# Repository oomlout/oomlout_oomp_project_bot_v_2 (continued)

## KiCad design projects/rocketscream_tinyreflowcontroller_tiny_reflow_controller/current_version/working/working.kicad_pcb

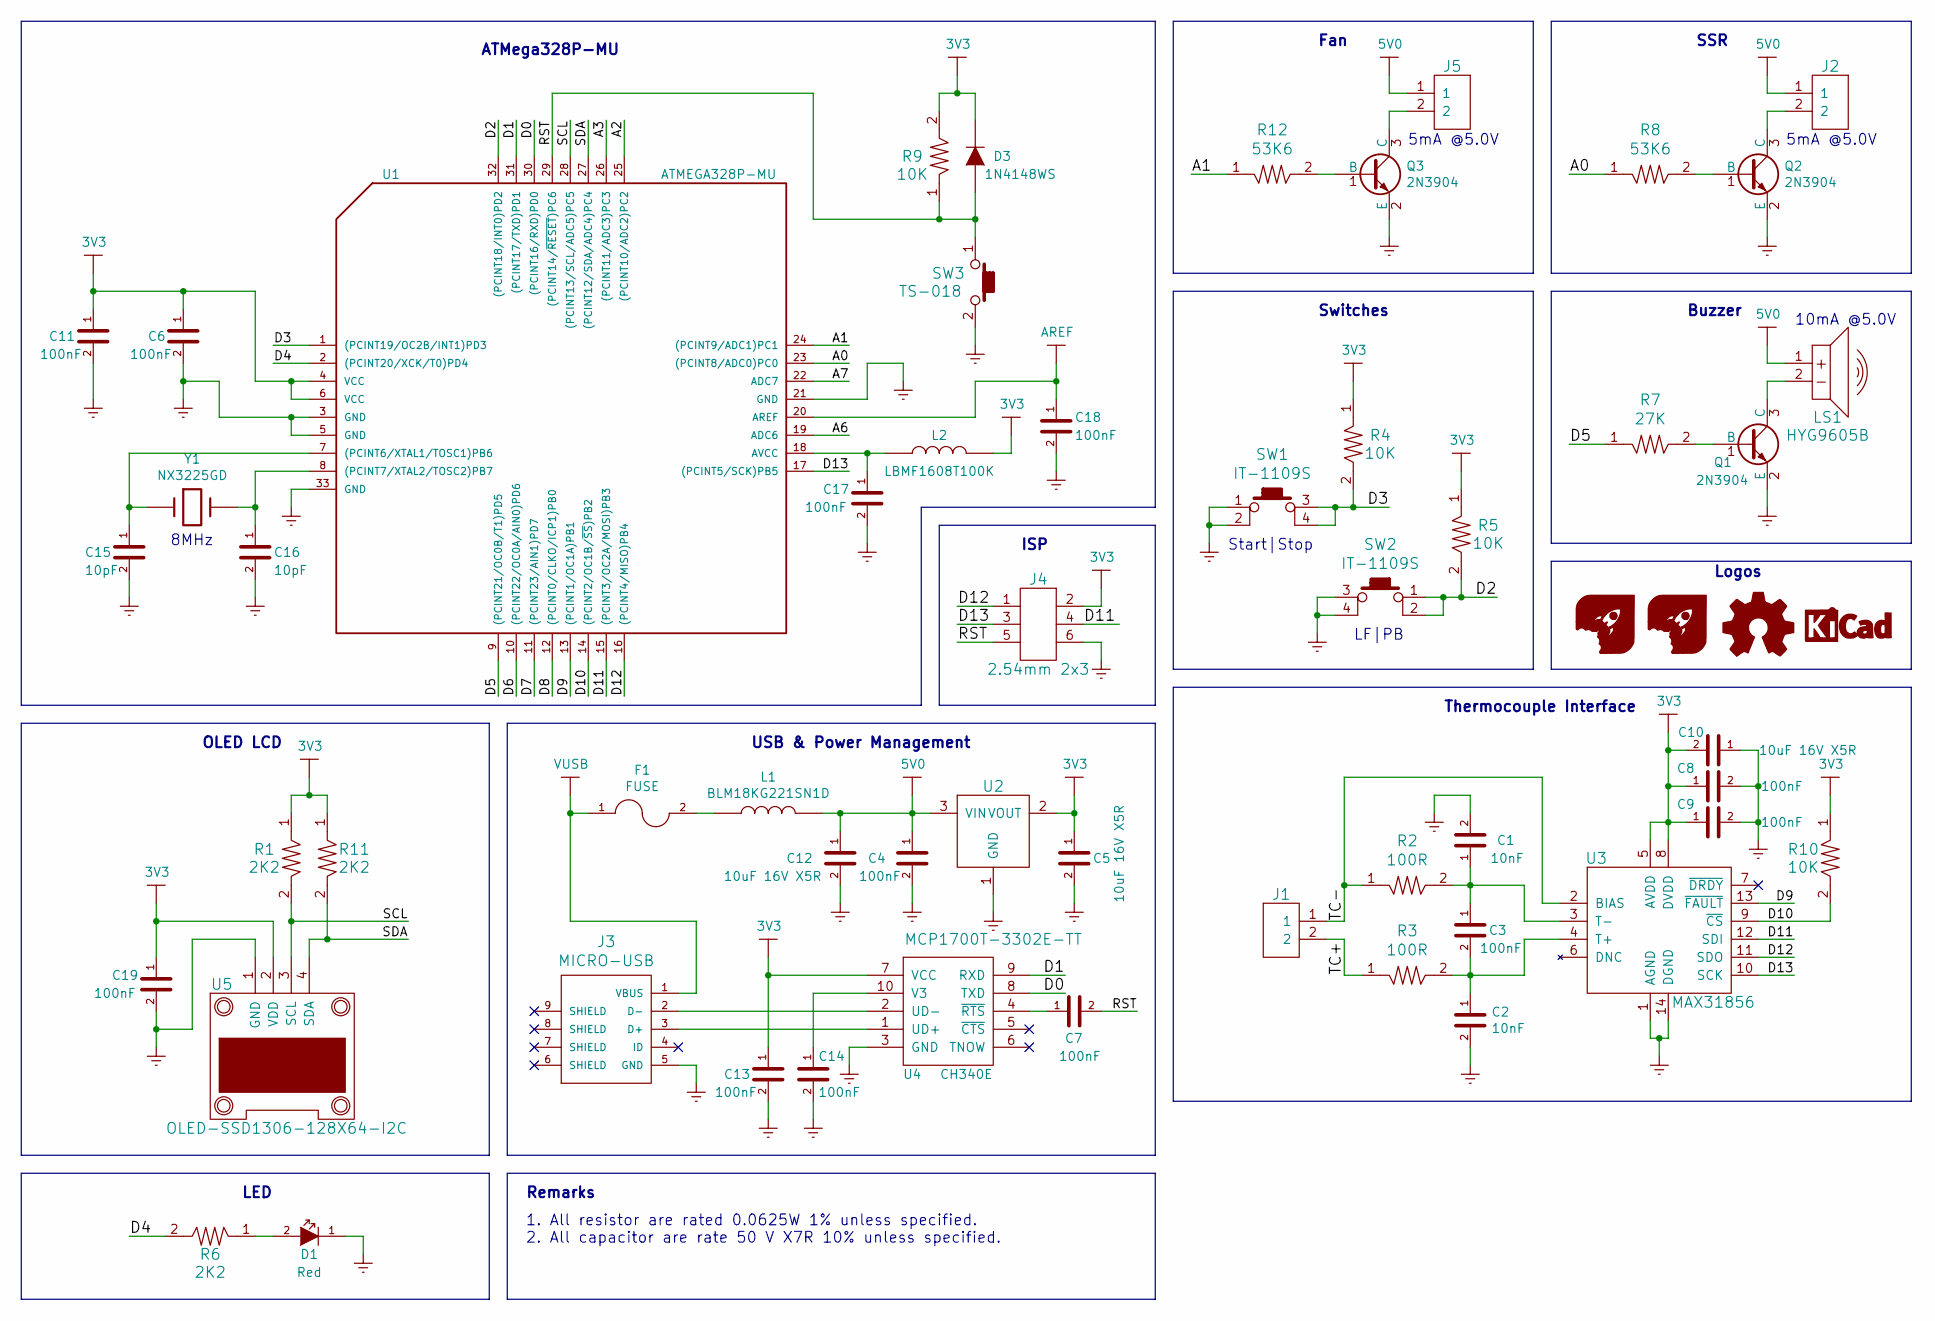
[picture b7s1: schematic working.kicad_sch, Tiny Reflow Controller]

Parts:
C1, C2: 10nF; C_0603
C3, C4, C6, C7, C8, C9, C11, C13, C14, C17, C18, C19: 100nF; C_0603
C5, C10, C12: 10uF 16V X5R; C_0603
C15, C16: 10pF; C_0603
D1: Red; LED_0603
D3: 1N4148WS; SOD-323
F1: FUSE; MF-FSMF
J1, J2, J5: TERMINAL-BLOCK-1x2; TB-1776275-2
J3: MICRO-USB
J4: 2.54mm 2x3; HDR_2x3_Pitch2.54mm
L1: BLM18KG221SN1D; I_0603
L2: LBMF1608T100K; I_0603
LOGO1: LOGO-ROCKET-SCREAM; LOGO-ROCKET-SCREAM_Without_Text_XXXSmall
LOGO2: LOGO-KICAD; LOGO-KICAD_XSmall
LOGO3: LOGO-ROCKET-SCREAM; LOGO-ROCKET-SCREAM_Vertical_Small
LOGO4: LOGO-OSHW; LOGO-OSHW_Small
LS1: HYG9605B
Q1, Q2, Q3: 2N3904; SOT-23
R1, R6, R11: 2K2; R_0603
R2, R3: 100R; R_0603
R4, R5, R9, R10: 10K; R_0603
R7: 27K; R_0603
R8, R12: 53K6; R_0603
SW1, SW2: IT-1109S; IT-1102W
SW3: TS-018
U1: ATMEGA328P-MU; QFN-32_5x5mm_Pitch0.5mm
U2: MCP1700T-3302E-TT; SOT-23
U3: MAX31856; TSSOP-14
U4: CH340E; MSOP-10
U5: OLED-SSD1306-128X64-I2C
Y1: NX3225GD

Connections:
3V3: C5.1, C6.1, C8.1, C9.1, C10.2, C11.1, C13.1, C19.1, D3.1 (K), J4.2, L2.2, R1.1, R4.1, R5.1, R9.2, R10.1, R11.1, U1.4 (VCC), U1.6 (VCC), U2.2 (VOUT), U3.5 (AVDD), U3.8 (DVDD), U4.7 (VCC), U5.2 (VDD)
5V0: C4.1, C12.1, J2.1, J5.1, L1.2, LS1.1, U2.3 (VIN)
/A0: R8.1, U1.23 ((PCINT8/ADC0)PC0)
/A1: R12.1, U1.24 ((PCINT9/ADC1)PC1)
/A2: U1.25 ((PCINT10/ADC2)PC2)
/A3: U1.26 ((PCINT11/ADC3)PC3)
/A6: U1.19 (ADC6)
/A7: U1.22 (ADC7)
/D0: U1.30 ((PCINT16/RXD)PD0), U4.8 (TXD)
/D1: U1.31 ((PCINT17/TXD)PD1), U4.9 (RXD)
/D2: R5.2, SW2.1, SW2.2, U1.32 ((PCINT18/INT0)PD2)
/D3: R4.2, SW1.3, SW1.4, U1.1 ((PCINT19/OC2B/INT1)PD3)
/D4: R6.2, U1.2 ((PCINT20/XCK/T0)PD4)
/D5: R7.1, U1.9 ((PCINT21/OC0B/T1)PD5)
/D6: U1.10 ((PCINT22/OC0A/AIN0)PD6)
/D7: U1.11 ((PCINT23/AIN1)PD7)
/D8: U1.12 ((PCINT0/CLKO/ICP1)PB0)
/D9: U1.13 ((PCINT1/OC1A)PB1), U3.13 (~FAULT)
/D10: R10.2, U1.14 ((PCINT2/OC1B/~SS)PB2), U3.9 (~CS)
/D11: J4.4, U1.15 ((PCINT3/OC2A/MOSI)PB3), U3.12 (SDI)
/D12: J4.1, U1.16 ((PCINT4/MISO)PB4), U3.11 (SDO)
/D13: J4.3, U1.17 ((PCINT5/SCK)PB5), U3.10 (SCK)
/RST: C7.2, D3.2 (A), J4.5, R9.1, SW3.1, U1.29 ((PCINT14/~RESET)PC6)
/SCL: R1.2, U1.28 ((PCINT13/SCL/ADC5)PC5), U5.3 (SCL)
/SDA: R11.2, U1.27 ((PCINT12/SDA/ADC4)PC4), U5.4 (SDA)
/TC+: J1.2, R3.1
/TC-: J1.1, R2.1, U3.2 (BIAS)
AREF: C18.1, U1.20 (AREF)
GND: C1.2, C2.2, C4.2, C5.2, C6.2, C8.2, C9.2, C10.1, C11.2, C12.2, C13.2, C14.2, C15.2, C16.2, C17.2, C18.2, C19.2, D1.1 (K), J3.5 (GND), J4.6, Q1.2 (E), Q2.2 (E), Q3.2 (E), SW1.1, SW1.2, SW2.3, SW2.4, SW3.2, U1.3 (GND), U1.5 (GND), U1.21 (GND), U1.33 (GND), U2.1 (GND), U3.1 (AGND), U3.14 (DGND), U4.3 (GND), U5.1 (GND)
unnamed: C1.1, C3.1, R2.2, U3.3 (T-)
unnamed: C2.1, C3.2, R3.2, U3.4 (T+)
unnamed: C7.1, U4.4 (~RTS)
unnamed: C14.1, U4.10 (V3)
unnamed: C15.1, U1.7 ((PCINT6/XTAL1/TOSC1)PB6), Y1.1
unnamed: C16.1, U1.8 ((PCINT7/XTAL2/TOSC2)PB7), Y1.2
unnamed: C17.1, L2.1, U1.18 (AVCC)
unnamed: D1.2 (A), R6.1
unnamed: F1.2, L1.1
unnamed: J2.2, Q2.3 (C)
unnamed: J3.2 (D-), U4.2 (UD-)
unnamed: J3.3 (D+), U4.1 (UD+)
unnamed: J5.2, Q3.3 (C)
unnamed: LS1.2, Q1.3 (C)
unnamed: Q1.1 (B), R7.2
unnamed: Q2.1 (B), R8.2
unnamed: Q3.1 (B), R12.2
VUSB: F1.1, J3.1 (VBUS)

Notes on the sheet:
LED
8MHz
Logos
ISP
Remarks
ATMega328P-MU
OLED LCD
LF|PB
Thermocouple Interface
Switches
1. All resistor are rated 0.0625W 1% unless specified. 2. All capacitor are rate 50 V X7R 10% unless specified.
Fan
SSR
10mA @5.0V
Start|Stop
5mA @5.0V
USB & Power Management
Buzzer

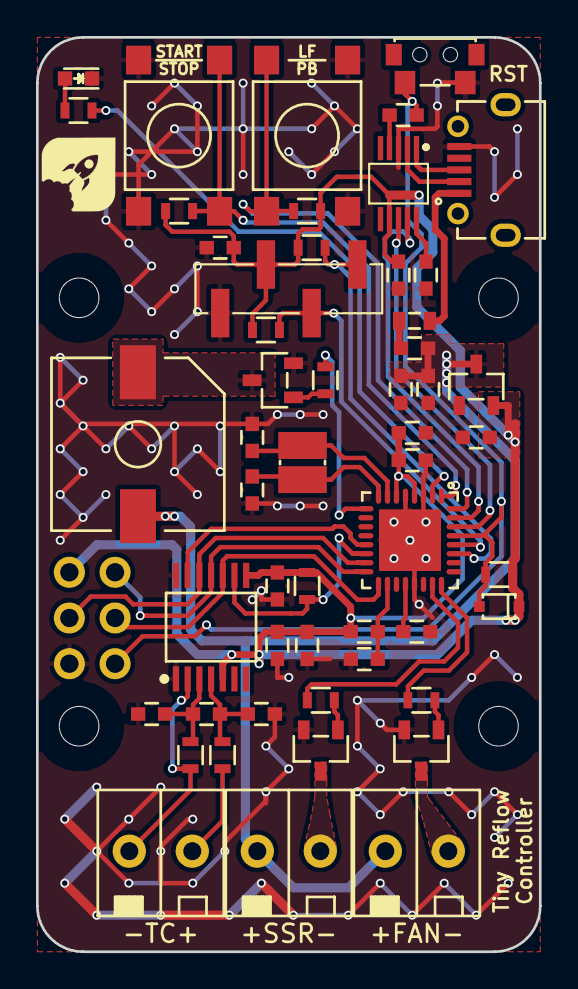
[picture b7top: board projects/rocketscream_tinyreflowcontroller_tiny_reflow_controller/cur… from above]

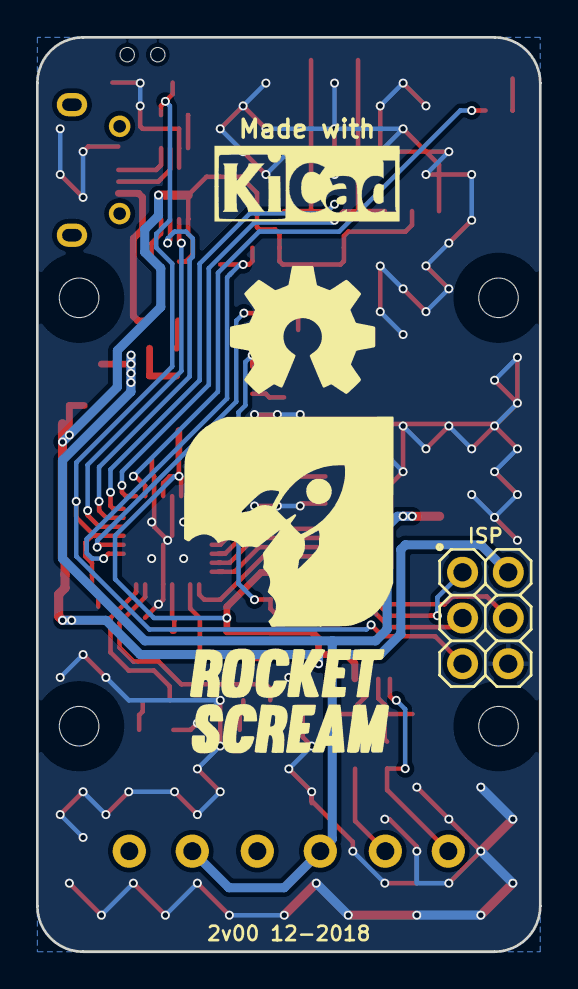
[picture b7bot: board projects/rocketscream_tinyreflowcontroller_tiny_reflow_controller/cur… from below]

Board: 2 copper layers, 27.9 x 50.8 mm, 58 parts (4 on the bottom side), 40 nets.

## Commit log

2023-09-07 comitting after 1 generations
2023-09-07 working on code
2023-09-07 more eagle to kicad
2023-09-08 all brought together
2023-09-09 project generations
2023-09-09 Updating readmes and images
2023-09-09 comitting after 100 generations
2023-09-10 new readmes and image resolutions.
2023-09-10 position test
2023-09-10 added mounting holes
2023-09-10 readme fix
2023-09-10 getting up to date
2023-09-13 added generate doc
2023-09-13 first run through
2023-09-14 some workings.
2023-09-15 comitting after 200 generations
2023-09-22 some works
2023-10-08 working on gens
